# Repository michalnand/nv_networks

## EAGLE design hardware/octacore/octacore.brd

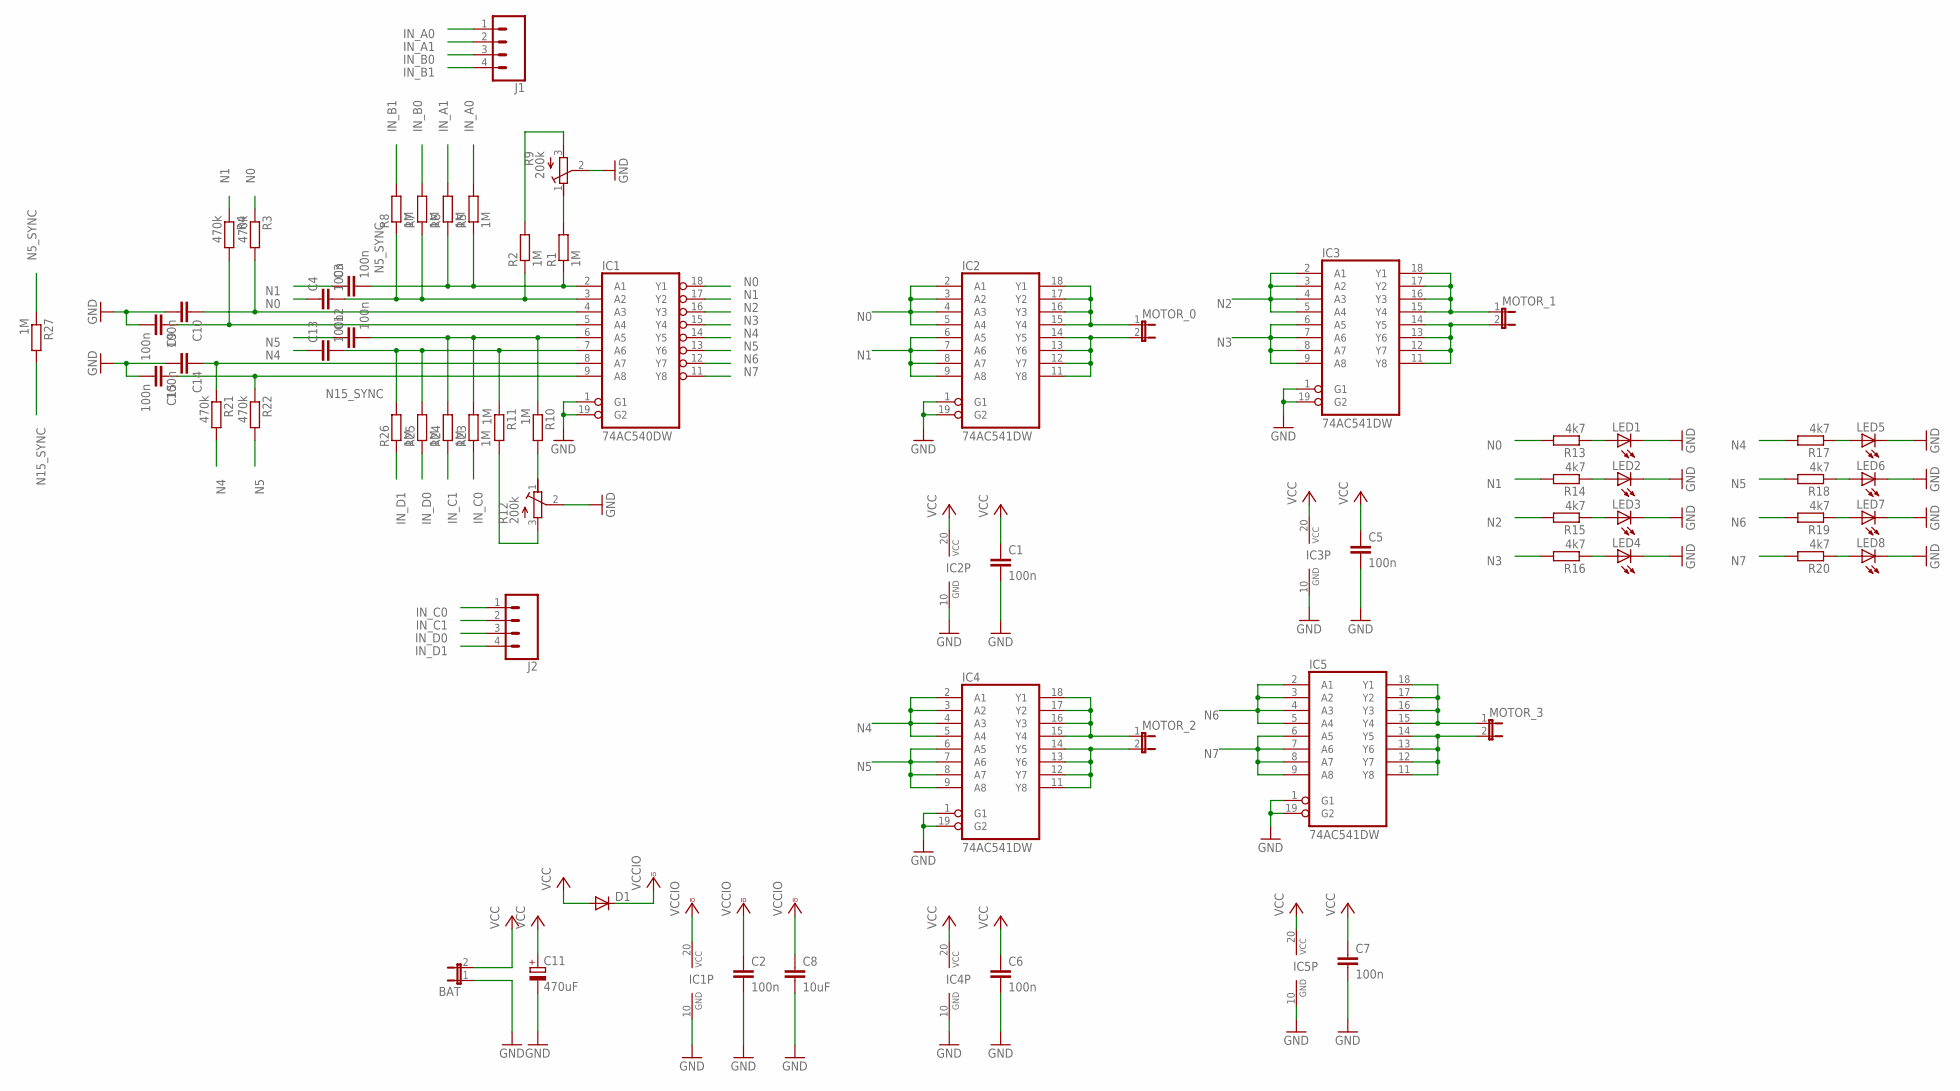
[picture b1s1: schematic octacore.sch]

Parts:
BAT: JUMPER_JP1E; JUMPER_JP1
C1, C2, C3, C4, C5, C6, C7, C9, C10, C12, C13, C14, C15: 100n; C0805
C8: 10uF; C0805
C11: 470uF; 140CLH-1010
D1: DIODE-DO214AA; DO214AA
IC1: 74AC540DW; SO20W
IC2, IC3, IC4, IC5: 74AC541DW; SO20W
J1, J2: CONN_04; 1X04
LED1, LED2, LED3, LED4, LED5, LED6, LED7, LED8: LEDSML1206; SML1206
MOTOR_0, MOTOR_1, MOTOR_2, MOTOR_3: JUMPER_JP1E; JUMPER_JP1
R1, R2, R5, R6, R7, R8, R10, R11, R23, R24, R25, R26, R27: 1M; M0805
R3, R4, R21, R22: 470k; M0805
R9, R12: 200k; RTRIM3314G
R13, R14, R15, R16, R17, R18, R19, R20: 4k7; M0805

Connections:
GND: BAT.1, C1.2, C2.2, C5.2, C6.2, C7.2, C8.2, C9.2, C10.2, C11.-, C14.2, C15.2, IC1.1 (G1), IC1.10 (GND), IC1.19 (G2), IC2.1 (G1), IC2.10 (GND), IC2.19 (G2), IC3.1 (G1), IC3.10 (GND), IC3.19 (G2), IC4.1 (G1), IC4.10 (GND), IC4.19 (G2), IC5.1 (G1), IC5.10 (GND), IC5.19 (G2), LED1.C, LED2.C, LED3.C, LED4.C, LED5.C, LED6.C, LED7.C, LED8.C, R9.2 (S), R12.2 (S)
IN_A0: J1.1, R5.2
IN_A1: J1.2, R6.2
IN_B0: J1.3, R7.2
IN_B1: J1.4, R8.2
IN_C0: J2.1, R23.1
IN_C1: J2.2, R24.1
IN_D0: J2.3, R25.1
IN_D1: J2.4, R26.1
N0: C4.1, IC1.18 (Y1), IC2.2 (A1), IC2.3 (A2), IC2.4 (A3), IC2.5 (A4), R3.1, R13.2
N1: C3.1, IC1.17 (Y2), IC2.6 (A5), IC2.7 (A6), IC2.8 (A7), IC2.9 (A8), R4.1, R14.2
N2: IC1.16 (Y3), IC3.2 (A1), IC3.3 (A2), IC3.4 (A3), IC3.5 (A4), R15.2
N3: IC1.15 (Y4), IC3.6 (A5), IC3.7 (A6), IC3.8 (A7), IC3.9 (A8), R16.2
N4: C13.1, IC1.14 (Y5), IC4.2 (A1), IC4.3 (A2), IC4.4 (A3), IC4.5 (A4), R17.2, R21.2
N5: C12.1, IC1.13 (Y6), IC4.6 (A5), IC4.7 (A6), IC4.8 (A7), IC4.9 (A8), R18.2, R22.2
N5_SYNC: C3.2, IC1.2 (A1), R1.1, R5.1, R6.1, R27.1
N6: IC1.12 (Y7), IC5.2 (A1), IC5.3 (A2), IC5.4 (A3), IC5.5 (A4), R19.2
N7: IC1.11 (Y8), IC5.6 (A5), IC5.7 (A6), IC5.8 (A7), IC5.9 (A8), R20.2
N15_SYNC: C12.2, IC1.6 (A5), R10.1, R23.2, R24.2, R27.2
unnamed: IC3.15 (Y4), IC3.16 (Y3), IC3.17 (Y2), IC3.18 (Y1), MOTOR_1.1
unnamed: IC3.11 (Y8), IC3.12 (Y7), IC3.13 (Y6), IC3.14 (Y5), MOTOR_1.2
unnamed: IC2.15 (Y4), IC2.16 (Y3), IC2.17 (Y2), IC2.18 (Y1), MOTOR_0.1
unnamed: IC2.11 (Y8), IC2.12 (Y7), IC2.13 (Y6), IC2.14 (Y5), MOTOR_0.2
unnamed: R10.2, R12.1 (E)
unnamed: C4.2, IC1.3 (A2), R2.1, R7.1, R8.1
unnamed: IC4.15 (Y4), IC4.16 (Y3), IC4.17 (Y2), IC4.18 (Y1), MOTOR_2.1
unnamed: IC4.11 (Y8), IC4.12 (Y7), IC4.13 (Y6), IC4.14 (Y5), MOTOR_2.2
unnamed: IC5.15 (Y4), IC5.16 (Y3), IC5.17 (Y2), IC5.18 (Y1), MOTOR_3.1
unnamed: IC5.11 (Y8), IC5.12 (Y7), IC5.13 (Y6), IC5.14 (Y5), MOTOR_3.2
unnamed: C10.1, IC1.4 (A3), R3.2
unnamed: C9.1, IC1.5 (A4), R4.2
unnamed: R2.2, R9.3 (A)
unnamed: R1.2, R9.1 (E)
unnamed: C13.2, IC1.7 (A6), R11.1, R25.2, R26.2
unnamed: R11.2, R12.3 (A)
unnamed: LED2.A, R14.1
unnamed: LED1.A, R13.1
unnamed: LED3.A, R15.1
unnamed: LED4.A, R16.1
unnamed: LED5.A, R17.1
unnamed: LED6.A, R18.1
unnamed: LED7.A, R19.1
unnamed: LED8.A, R20.1
unnamed: C14.1, IC1.8 (A7), R21.1
unnamed: C15.1, IC1.9 (A8), R22.1
VCC: BAT.2, C1.1, C5.1, C6.1, C7.1, C11.+, D1.A, IC2.20 (VCC), IC3.20 (VCC), IC4.20 (VCC), IC5.20 (VCC)
VCCIO: C2.1, C8.1, D1.C, IC1.20 (VCC)

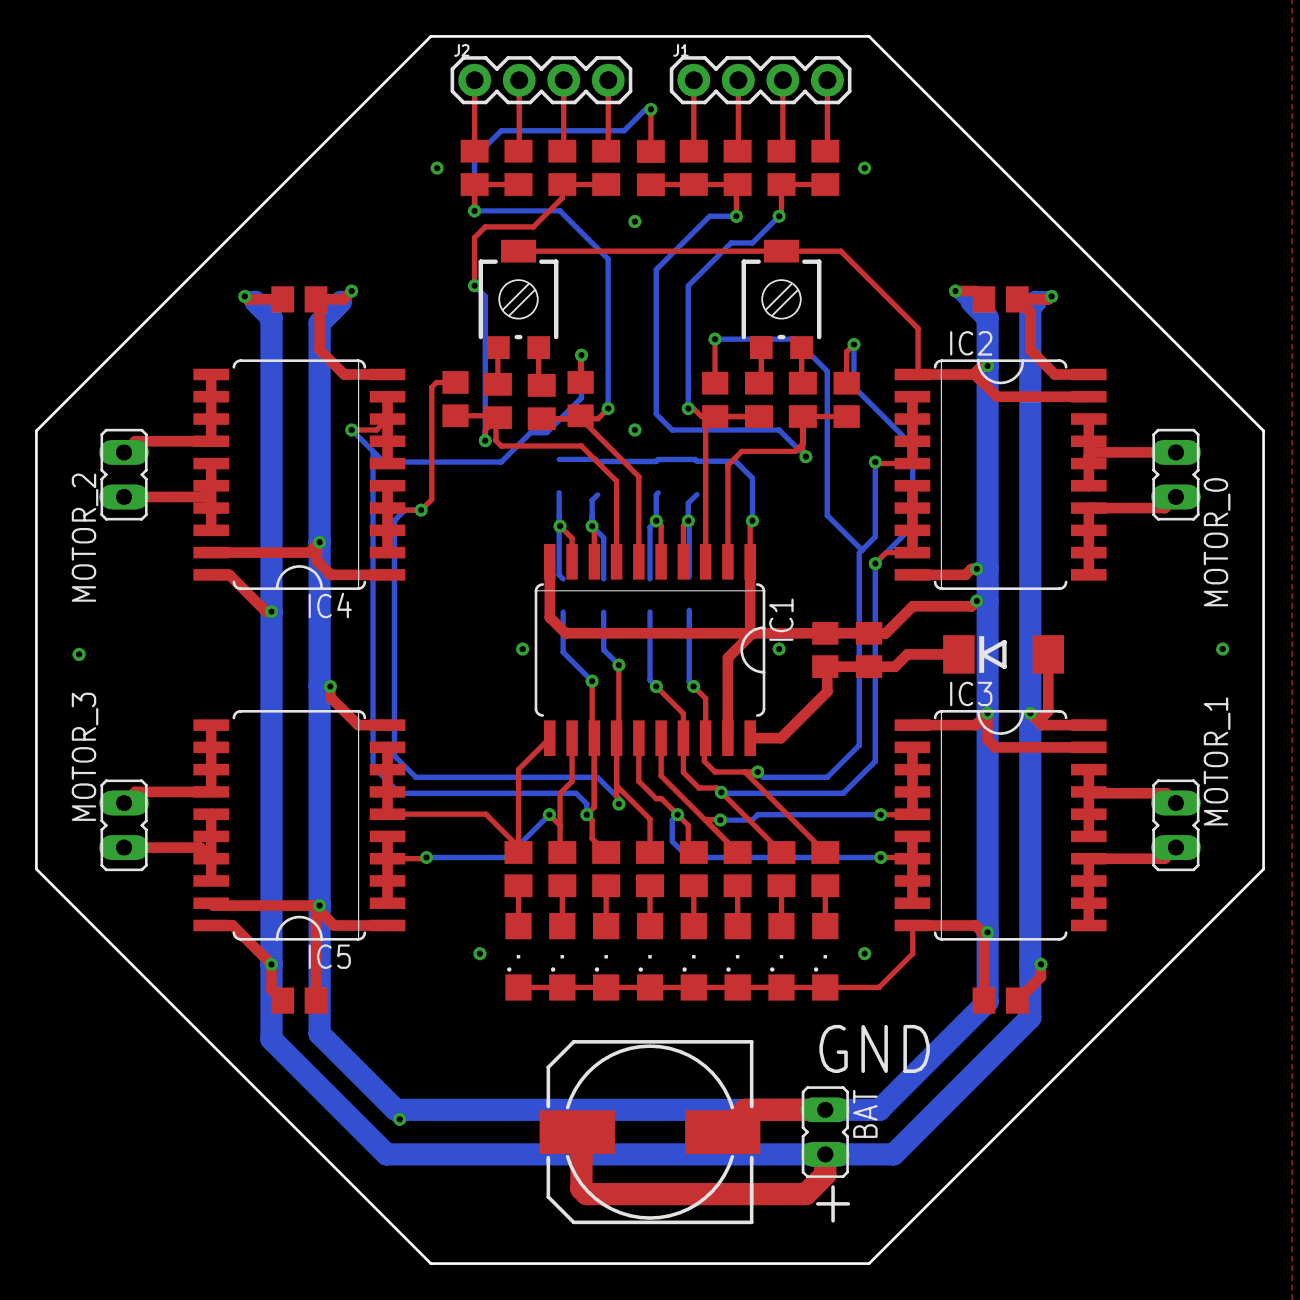
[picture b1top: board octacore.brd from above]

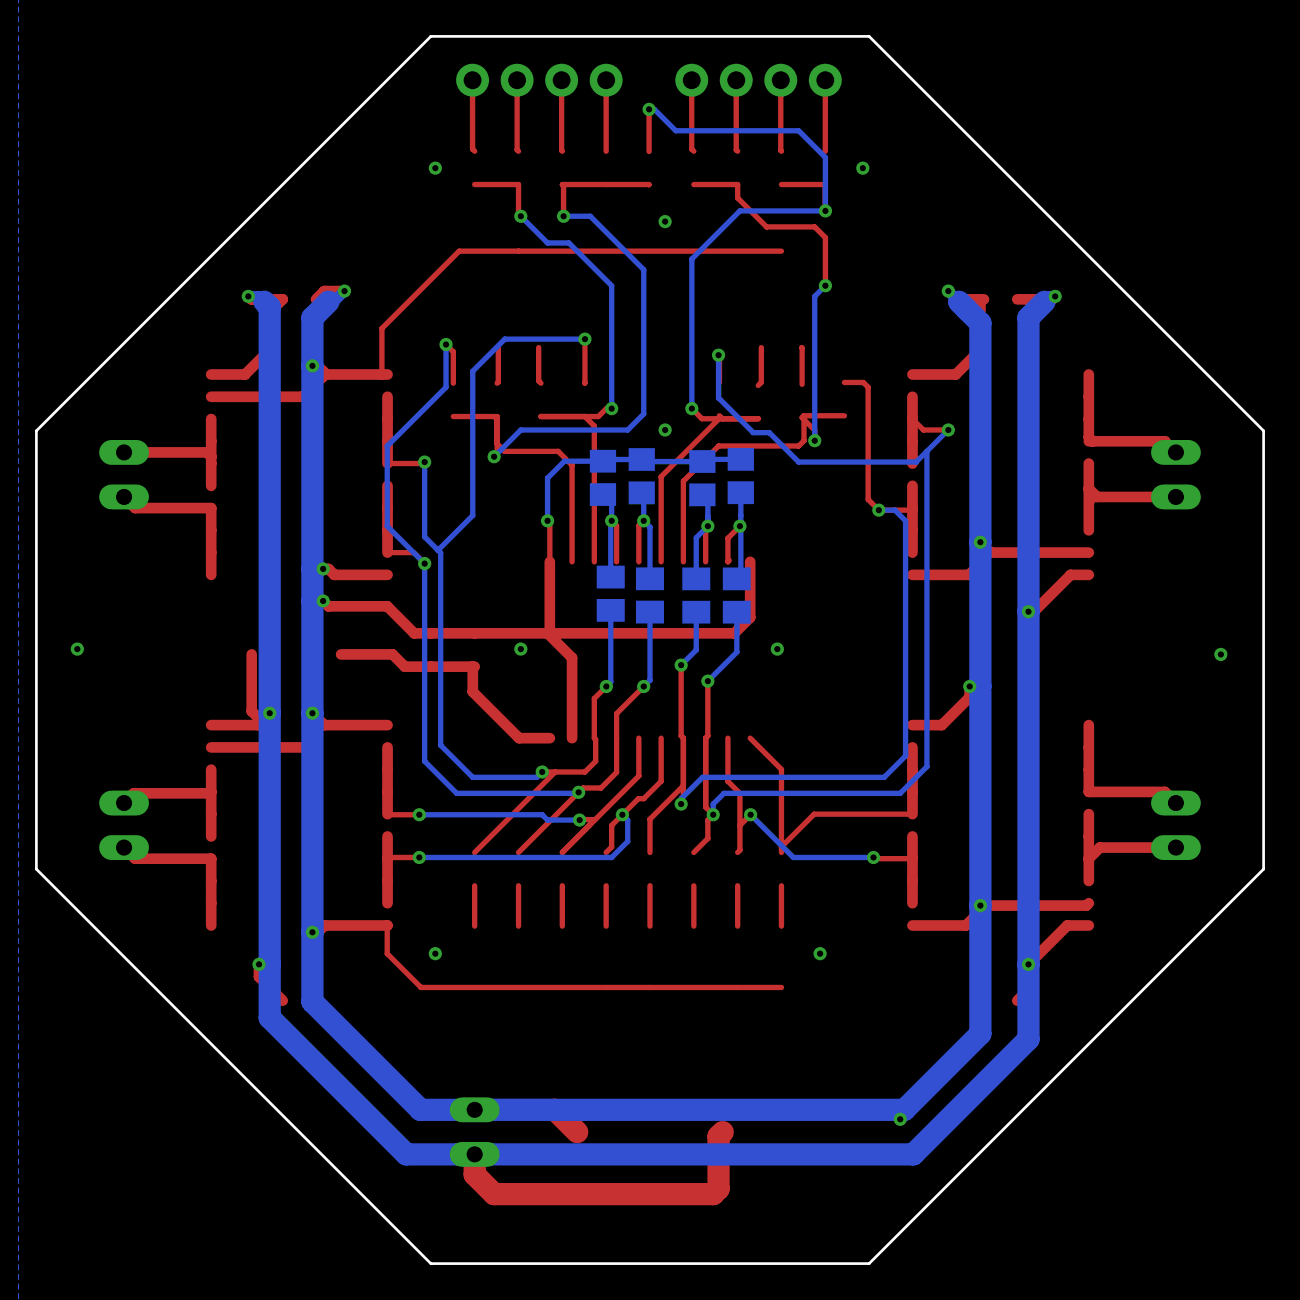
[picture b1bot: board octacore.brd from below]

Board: 2 copper layers, 70.0 x 70.0 mm, 63 parts (8 on the bottom side), 47 nets.

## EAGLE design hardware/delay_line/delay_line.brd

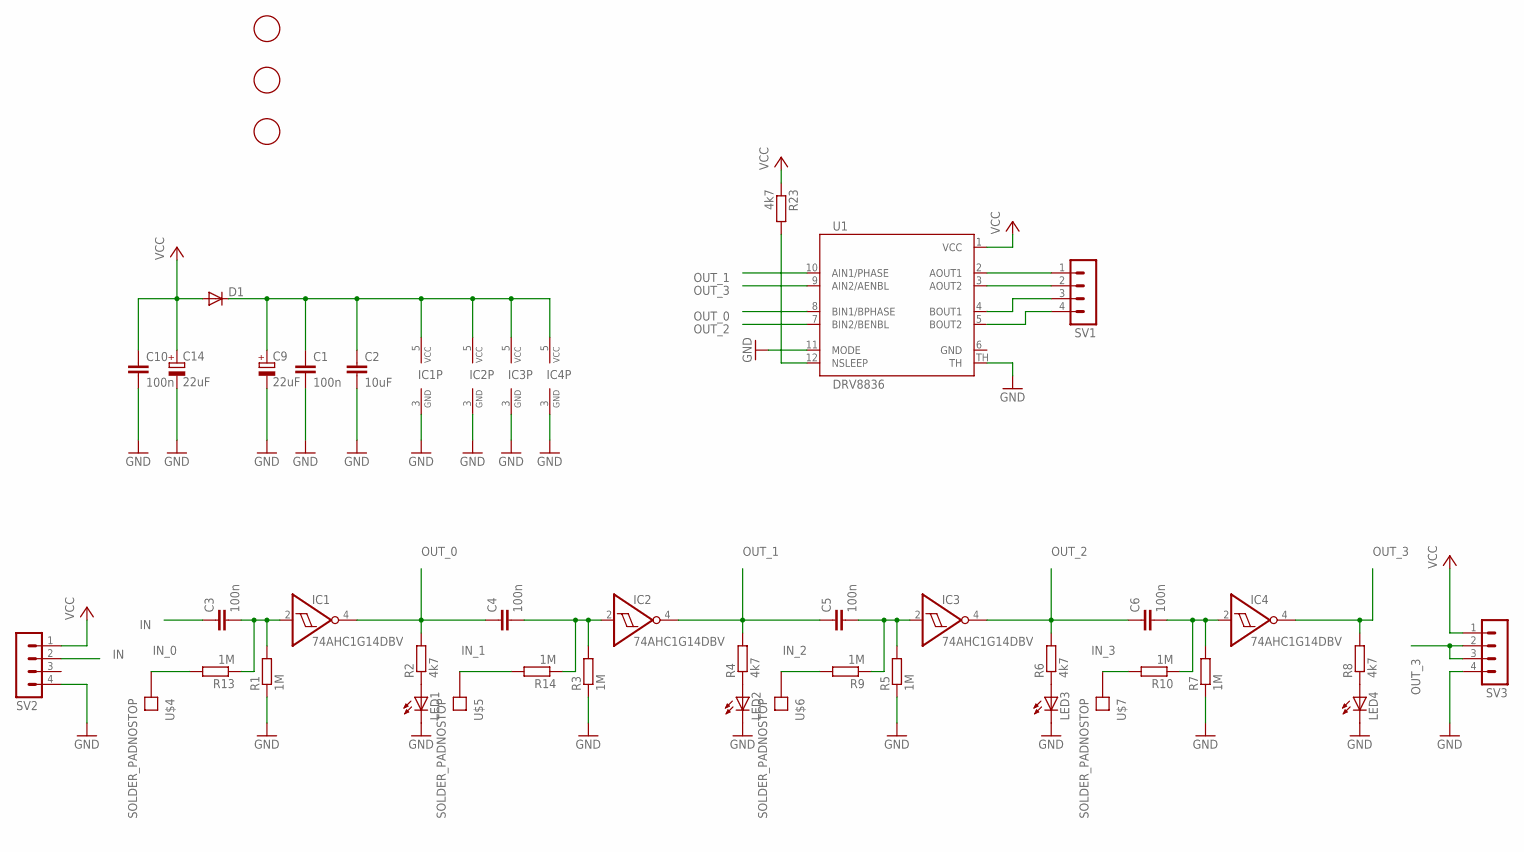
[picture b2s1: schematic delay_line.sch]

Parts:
C1, C3, C4, C5, C6, C10: 100n; C0805
C2: 10uF; C0805
C9, C14: 22uF; 153CLV-0605
D1: DIODE-DO214AA; DO214AA
IC1, IC2, IC3, IC4: 74AHC1G14DBV; SOT23-5
LED1, LED2, LED3, LED4: LEDSML1206; SML1206
R1, R3, R5, R7, R9, R10, R13, R14: 1M; M0805
R2, R4, R6, R8, R23: 4k7; M0805
SV1, SV2, SV3: MA04-1
U1: DRV8836; 12WSON
U$1, U$2, U$3: ADAFRUIT_FIDUCIAL; ADAFRUIT_FIDUCIAL_1MM
U$4, U$5, U$6, U$7: SOLDER_PADNOSTOP; SOLDER_PAD_NOSTOP

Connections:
GND: C1.2, C2.2, C9.-, C10.2, C14.-, IC1.3 (GND), IC2.3 (GND), IC3.3 (GND), IC4.3 (GND), LED1.C, LED2.C, LED3.C, LED4.C, R1.1, R3.1, R5.1, R7.1, SV2.4, SV3.4, U1.11 (MODE), U1.TH
IN: C3.1, SV2.2
IN_0: R13.2, U$4.SPAD
IN_1: R14.2, U$5.SPAD
IN_2: R9.2, U$6.SPAD
IN_3: R10.2, U$7.SPAD
unnamed: C1.1, C2.1, C9.+, D1.C, IC1.5 (VCC), IC2.5 (VCC), IC3.5 (VCC), IC4.5 (VCC)
unnamed: C3.2, IC1.2 (I), R1.2, R13.1
unnamed: C5.2, IC3.2 (I), R5.2, R9.1
unnamed: C4.2, IC2.2 (I), R3.2, R14.1
unnamed: LED1.A, R2.1
unnamed: LED3.A, R6.1
unnamed: LED2.A, R4.1
unnamed: C6.2, IC4.2 (I), R7.2, R10.1
unnamed: LED4.A, R8.1
unnamed: SV1.4, U1.5 (BOUT2)
unnamed: SV1.3, U1.4 (BOUT1)
unnamed: R23.2, U1.12 (NSLEEP)
unnamed: SV1.2, U1.3 (AOUT2)
unnamed: SV1.1, U1.2 (AOUT1)
OUT_0: C4.1, IC1.4 (O), R2.2, U1.8 (BIN1/BPHASE)
OUT_1: C5.1, IC2.4 (O), R4.2, U1.10 (AIN1/PHASE)
OUT_2: C6.1, IC3.4 (O), R6.2, U1.7 (BIN2/BENBL)
OUT_3: IC4.4 (O), R8.2, SV3.2, SV3.3, U1.9 (AIN2/AENBL)
VCC: C10.1, C14.+, D1.A, R23.1, SV2.1, SV3.1, U1.1 (VCC)

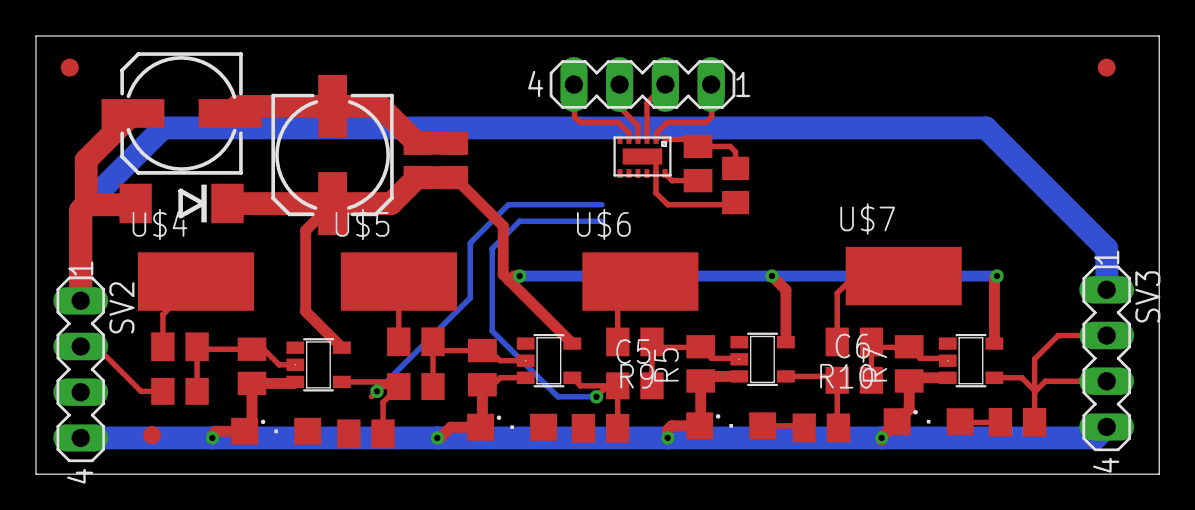
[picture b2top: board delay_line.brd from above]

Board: 2 copper layers, 62.4 x 24.3 mm, 42 parts (0 on the bottom side), 25 nets.

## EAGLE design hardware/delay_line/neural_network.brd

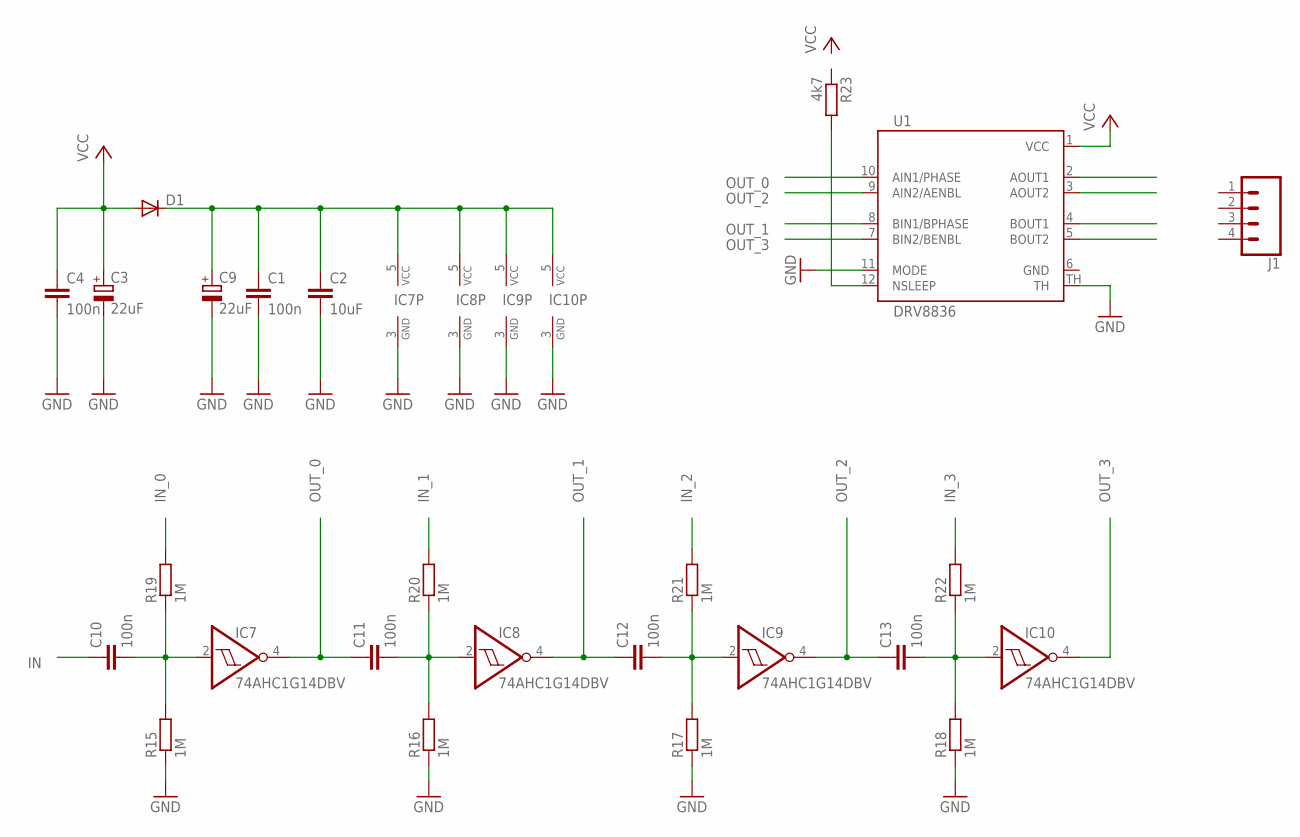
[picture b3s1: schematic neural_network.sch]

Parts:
C1, C4, C10, C11, C12, C13: 100n; C0805
C2: 10uF; C0805
C3, C9: 22uF; 153CLV-0605
D1: DIODE-DO214AA; DO214AA
IC7, IC8, IC9, IC10: 74AHC1G14DBV; SOT23-5
J1: CONN_04; 1X04
R15, R16, R17, R18, R19, R20, R21, R22: 1M; M0805
R23: 4k7; M0805
U1: DRV8836; 12WSON

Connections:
GND: C1.2, C2.2, C3.-, C4.2, C9.-, IC7.3 (GND), IC8.3 (GND), IC9.3 (GND), IC10.3 (GND), R15.1, R16.1, R17.1, R18.1, U1.11 (MODE), U1.TH
IN: C10.1
IN_0: R19.2
IN_1: R20.2
IN_2: R21.2
IN_3: R22.2
unnamed: C1.1, C2.1, C9.+, D1.C, IC7.5 (VCC), IC8.5 (VCC), IC9.5 (VCC), IC10.5 (VCC)
unnamed: C10.2, IC7.2 (I), R15.2, R19.1
unnamed: C11.2, IC8.2 (I), R16.2, R20.1
unnamed: C12.2, IC9.2 (I), R17.2, R21.1
unnamed: C13.2, IC10.2 (I), R18.2, R22.1
unnamed: R23.2, U1.12 (NSLEEP)
OUT_0: C11.1, IC7.4 (O), U1.10 (AIN1/PHASE)
OUT_1: C12.1, IC8.4 (O), U1.8 (BIN1/BPHASE)
OUT_2: C13.1, IC9.4 (O), U1.9 (AIN2/AENBL)
OUT_3: IC10.4 (O), U1.7 (BIN2/BENBL)
VCC: C3.+, C4.1, D1.A, U1.1 (VCC)

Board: 2 copper layers, 25 parts (0 on the bottom side), 12 nets, no tracks yet.

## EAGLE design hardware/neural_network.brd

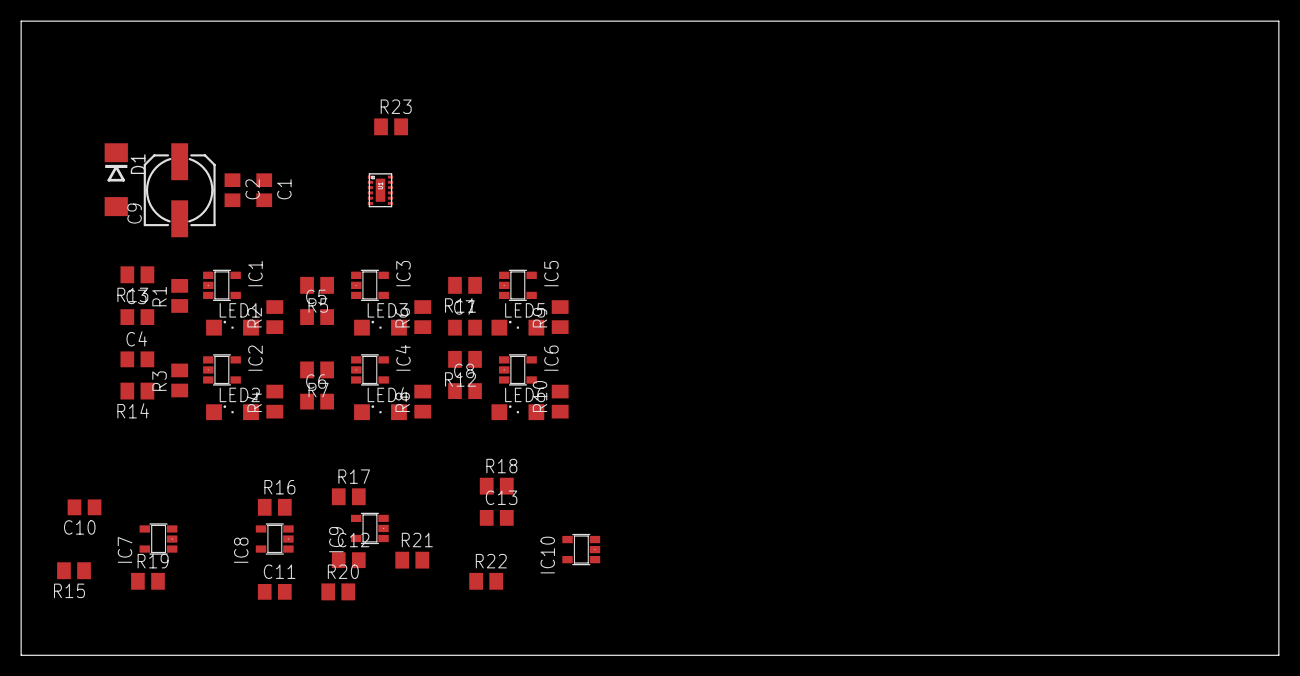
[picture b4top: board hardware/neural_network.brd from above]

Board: 2 copper layers, 119.0 x 60.0 mm, 54 parts (0 on the bottom side), 26 nets, no tracks yet.

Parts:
C1, C3, C4, C5, C6, C7, C8, C10, C11, C12, C13: 100n; C0805
C2: 10uF; C0805
C9: 22uF; 153CLV-0605
D1: DO214AA
IC1, IC2, IC3, IC4, IC5, IC6, IC7, IC8, IC9, IC10: 74AHC1G14DBV; SOT23-5
LED1, LED2, LED3, LED4, LED5, LED6: SML1206
R1, R3, R5, R7, R11, R12, R13, R14, R15, R16, R17, R18, R19, R20, R21, R22: 1M; M0805
R2, R4, R6, R8, R9, R10, R23: 4k7; M0805
U1: DRV8836; 12WSON

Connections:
B_OUT_0: C4.1, IC1.4, R2.2, R5.2, U1.10
B_OUT_1: C3.1, IC2.4, R4.2, R7.2, U1.9
GND: C1.2, C2.2, C5.1, C6.1, C7.1, C8.1, C9.-, IC1.3, IC2.3, IC3.3, IC4.3, IC5.3, IC6.3, IC7.3, IC8.3, IC9.3, IC10.3, LED1.C, LED2.C, LED3.C, LED4.C, LED5.C, LED6.C, R1.1, R3.1, R15.1, R16.1, R17.1, R18.1, U1.11, U1.TH
unnamed: C1.1, C2.1, C9.+, D1.C, IC1.5, IC2.5, IC3.5, IC4.5, IC5.5, IC6.5
unnamed: C3.2, IC1.2, R1.2, R13.1
unnamed: C5.2, IC3.2, R5.1
unnamed: C4.2, IC2.2, R3.2, R14.1
unnamed: LED1.A, R2.1
unnamed: LED3.A, R6.1
unnamed: LED2.A, R4.1
unnamed: C6.2, IC4.2, R7.1
unnamed: LED4.A, R8.1
unnamed: C7.2, IC5.2, R11.1
unnamed: LED5.A, R9.1
unnamed: C8.2, IC6.2, R12.1
unnamed: LED6.A, R10.1
unnamed: C10.2, IC7.2, R15.2, R19.1
unnamed: C11.2, IC8.2, R16.2, R20.1
unnamed: C12.2, IC9.2, R17.2, R21.1
unnamed: C13.2, IC10.2, R18.2, R22.1
unnamed: R23.2, U1.12
S0_OUT_0: IC3.4, R6.2, R11.2, U1.8
S0_OUT_1: IC4.4, R8.2, R12.2, U1.7
S1_OUT_0: IC5.4, R9.2
S1_OUT_1: IC6.4, R10.2
VCC: D1.A, IC7.5, IC8.5, IC9.5, IC10.5, U1.1

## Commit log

2019-02-14 initial
2019-02-23 common
2019-02-26 board
2019-03-03 octacore

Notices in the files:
parts and their libraries:
SparkFun-Connectors: Licensing: Creative Commons ShareAlike 4.0 International - https://creativecommons.org/licenses/by-sa/4.0
